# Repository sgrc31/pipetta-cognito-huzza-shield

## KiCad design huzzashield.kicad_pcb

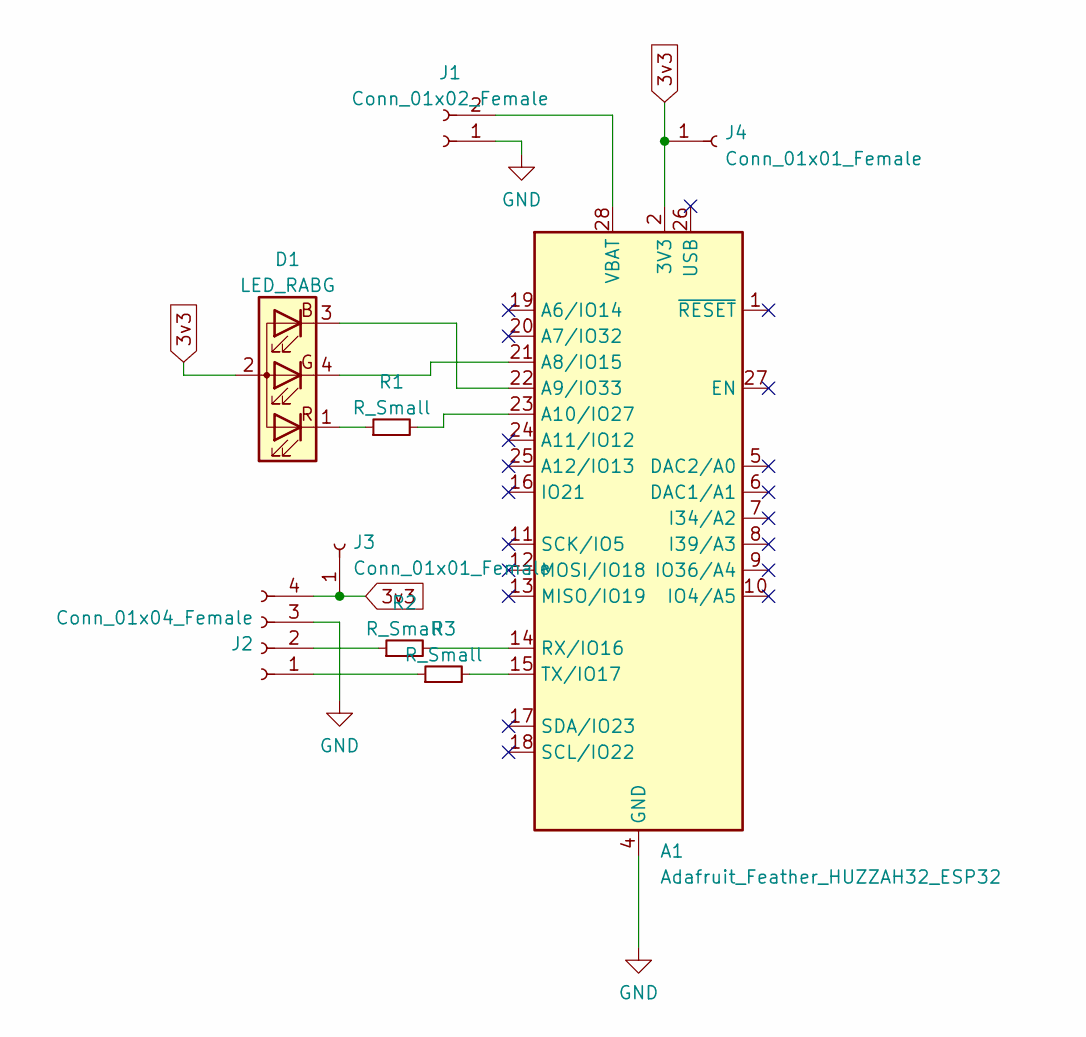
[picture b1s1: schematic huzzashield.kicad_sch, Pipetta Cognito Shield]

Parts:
A1: Adafruit_Feather_HUZZAH32_ESP32; FEATHERWING
D1: LED_RABG; LED_RGB_Cree_CLV1A-FKB_3.2x2.8mm
J1: Conn_01x02_Female; 1X02_LONGPADS
J2: Conn_01x04_Female; 1X04_LONGPADS
J3, J4: Conn_01x01_Female; PinHeader_1x01_P2.54mm_Vertical
R1, R2, R3: R_Small; R_1206_3216Metric_Pad1.30x1.75mm_HandSolder

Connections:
3v3: A1.2 (3V3), D1.2 (A), J2.4, J3.1, J4.1
GND: A1.4 (GND), J1.1, J2.3
unnamed: A1.14 (RX/IO16), R2.2
unnamed: A1.15 (TX/IO17), R3.2
unnamed: A1.21 (A8/IO15), D1.4 (GK)
unnamed: A1.22 (A9/IO33), D1.3 (BK)
unnamed: A1.23 (A10/IO27), R1.2
unnamed: A1.28 (VBAT), J1.2
unnamed: D1.1 (RK), R1.1
unnamed: J2.1, R3.1
unnamed: J2.2, R2.1

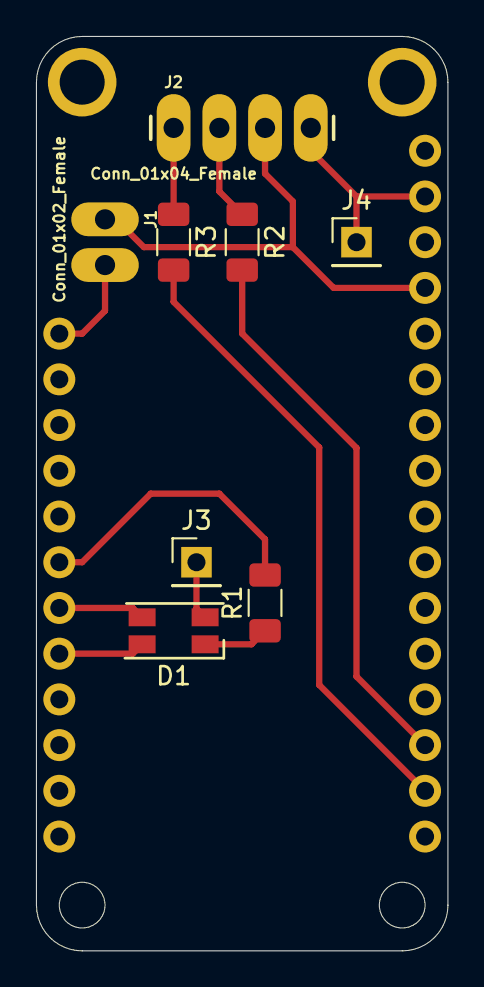
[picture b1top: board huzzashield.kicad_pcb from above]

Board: 2 copper layers, 22.9 x 50.8 mm, 9 parts (1 on the bottom side), 11 nets.

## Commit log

2022-06-23 Schematic ad pcb ready
